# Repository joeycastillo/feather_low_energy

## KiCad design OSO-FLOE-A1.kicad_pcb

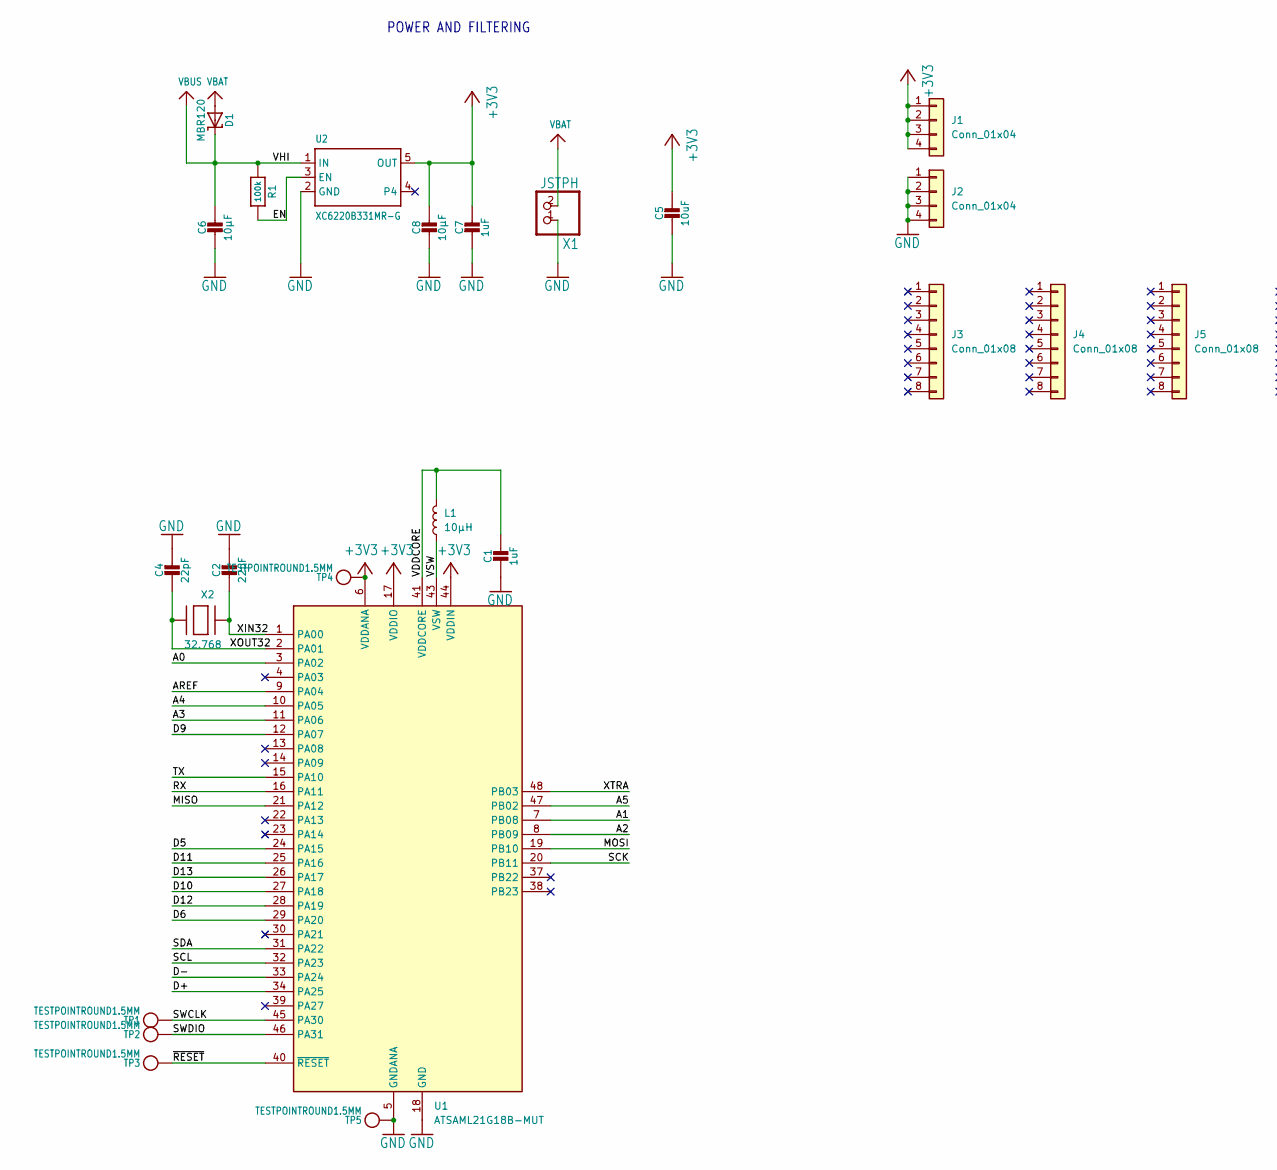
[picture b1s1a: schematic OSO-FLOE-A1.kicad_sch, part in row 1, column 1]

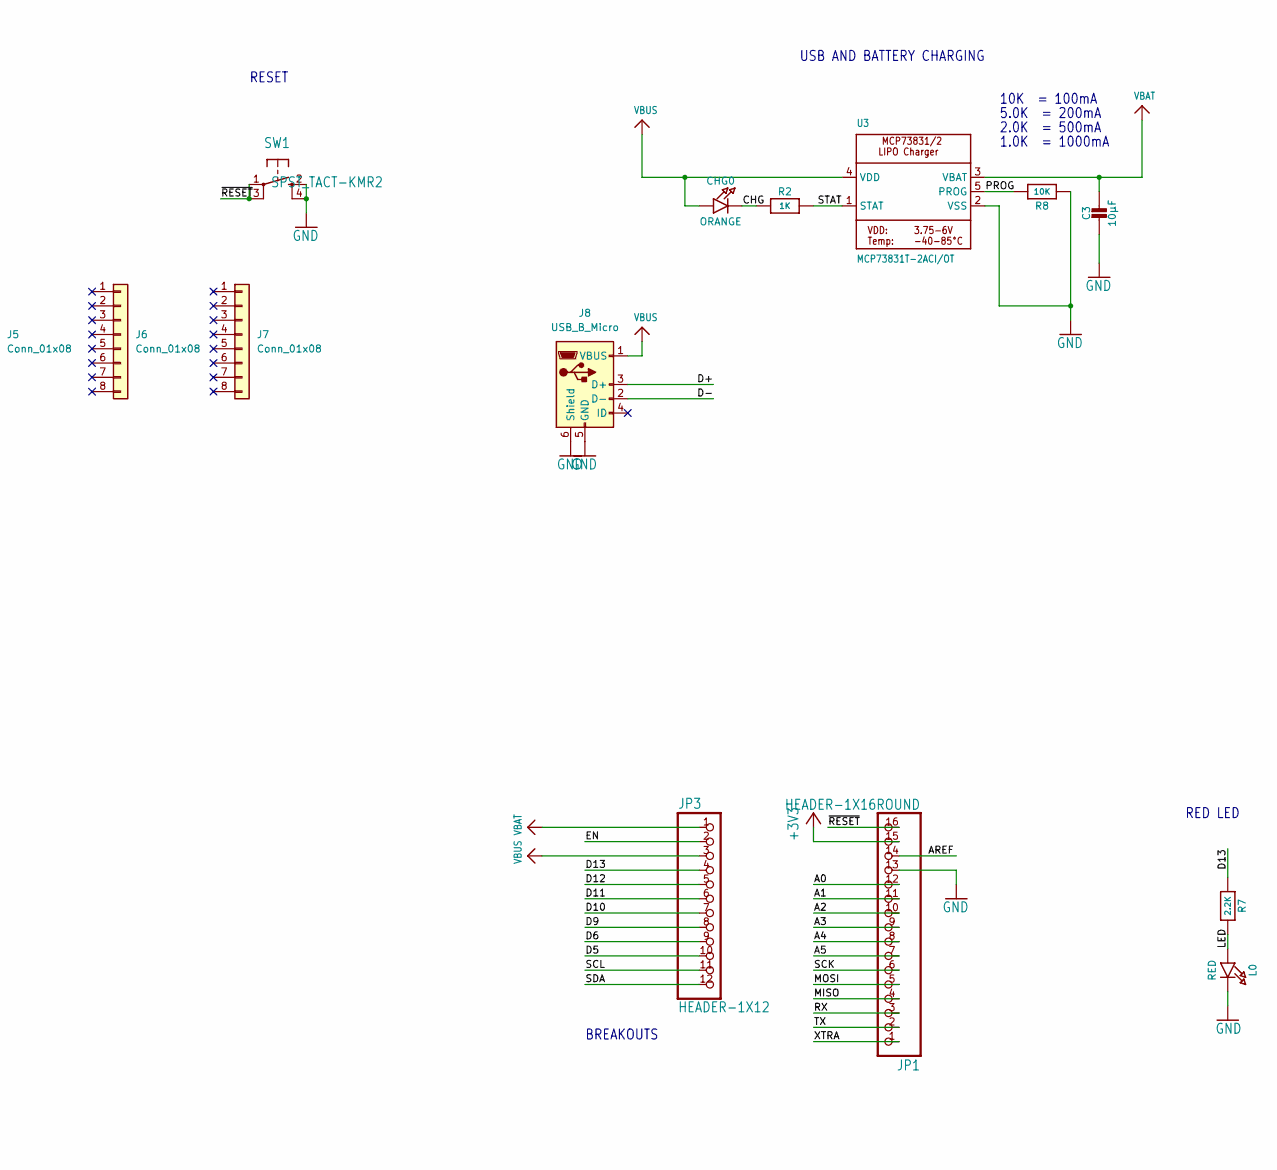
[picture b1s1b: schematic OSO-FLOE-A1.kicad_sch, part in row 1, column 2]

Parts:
C1, C7: 1uF; 0603-NO
C2, C4: 22pF; 0603-NO
C3, C6, C8: 10µF; 0805-NO
C5: 10uF; 0805-NO
CHG0: ORANGE; CHIPLED_0805_NOOUTLINE
D1: MBR120; SOD-123
J1, J2: Conn_01x04; PinHeader_1x04_P2.54mm_Vertical
J3, J4, J5, J6, J7: Conn_01x08; PinHeader_1x08_P2.54mm_Vertical
J8: USB_B_Micro; USB_Micro-B_Amphenol_10118194_Horizontal
JP1: HEADER-1X16ROUND; 1X16_ROUND
JP3: HEADER-1X12; 1X12_ROUND
L0: RED; CHIPLED_0805_NOOUTLINE
L1: 10µH; L_0805_2012Metric
R1: 100k; 0603-NO
R2: 1K; 0603-NO
R7: 2.2K; 0603-NO
R8: 10K; 0603-NO
SW1: SPST_TACT-KMR2; KMR2
TP1, TP2, TP3, TP4, TP5: TESTPOINTROUND1.5MM; TESTPOINT_ROUND_1.5MM
U1: ATSAML21G18B-MUT; QFN-48-1EP_7x7mm_P0.5mm_EP5.15x5.15mm
U2: XC6220B331MR-G; SOT23-5
U3: MCP73831T-2ACI/OT; SOT23-5
X1: JSTPH; JSTPH2
X2: 32.768; XTAL3215

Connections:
+3V3: C5.1, C7.1, C8.1, J1.1, J1.2, J1.3, J1.4, JP1.15, TP4.P$1, U1.6 (VDDANA), U1.17 (VDDIO), U1.36 (VDDIO), U1.44 (VDDIN), U2.5 (OUT)
/A0: JP1.12, U1.3 (PA02)
/A1: JP1.11, U1.7 (PB08)
/A2: JP1.10, U1.8 (PB09)
/A3: JP1.9, U1.11 (PA06)
/A4: JP1.8, U1.10 (PA05)
/A5: JP1.7, U1.47 (PB02)
/AREF: JP1.14, U1.9 (PA04)
/CHG: CHG0.C, R2.1
/D5: JP3.10, U1.24 (PA15)
/D6: JP3.9, U1.29 (PA20)
/D9: JP3.8, U1.12 (PA07)
/D10: JP3.7, U1.27 (PA18)
/D11: JP3.6, U1.25 (PA16)
/D12: JP3.5, U1.28 (PA19)
/D13: JP3.4, R7.1, U1.26 (PA17)
/D+: J8.3 (D+), U1.34 (PA25)
/D-: J8.2 (D-), U1.33 (PA24)
/EN: JP3.2, R1.2, U2.3 (EN)
/LED: L0.A, R7.2
/MISO: JP1.4, U1.21 (PA12)
/MOSI: JP1.5, U1.19 (PB10)
/PROG: R8.1, U3.5 (PROG)
/RX: JP1.3, U1.16 (PA11)
/SCK: JP1.6, U1.20 (PB11)
/SCL: JP3.11, U1.32 (PA23)
/SDA: JP3.12, U1.31 (PA22)
/STAT: R2.2, U3.1 (STAT)
/SWCLK: TP1.P$1, U1.45 (PA30)
/SWDIO: TP2.P$1, U1.46 (PA31)
/TX: JP1.2, U1.15 (PA10)
/VDDCORE: C1.1, L1.2, U1.41 (VDDCORE)
/VSW: L1.1, U1.43 (VSW)
/XIN32: C2.1, U1.1 (PA00), X2.P$1
/XOUT32: C4.1, U1.2 (PA01), X2.P$2
/XTRA: JP1.1, U1.48 (PB03)
/~RESET: JP1.16, SW1.1, SW1.3 (P1), TP3.P$1, U1.40 (~RESET)
GND: C1.2, C2.2, C3.2, C4.2, C5.2, C6.2, C7.2, C8.2, J2.1, J2.2, J2.3, J2.4, J8.5 (GND), J8.6 (Shield), JP1.13, L0.C, R8.2, SW1.2 (S), SW1.4 (S1), TP5.P$1, U1.5 (GNDANA), U1.18 (GND), U1.35 (GND), U1.42 (GND), U1.49, U2.2 (GND), U3.2 (VSS), X1.1
VBAT: C3.1, D1.A, JP3.1, U3.3 (VBAT), X1.2
VBUS: C6.1, CHG0.A, D1.C, J8.1 (VBUS), JP3.3, R1.1, U2.1 (IN), U3.4 (VDD)

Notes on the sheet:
RESET
2.0K = 500mA
10K = 100mA
5.0K = 200mA
POWER AND FILTERING
BREAKOUTS
1.0K = 1000mA
USB AND BATTERY CHARGING
RED LED

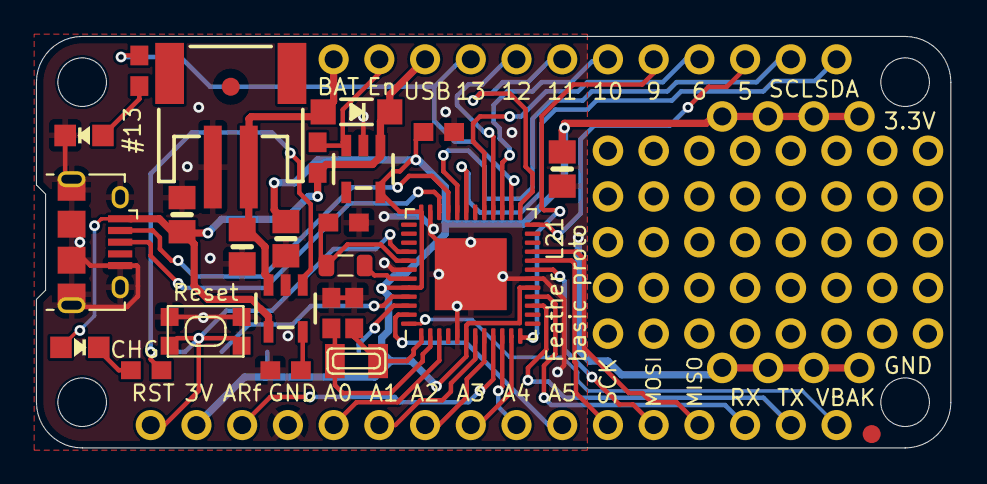
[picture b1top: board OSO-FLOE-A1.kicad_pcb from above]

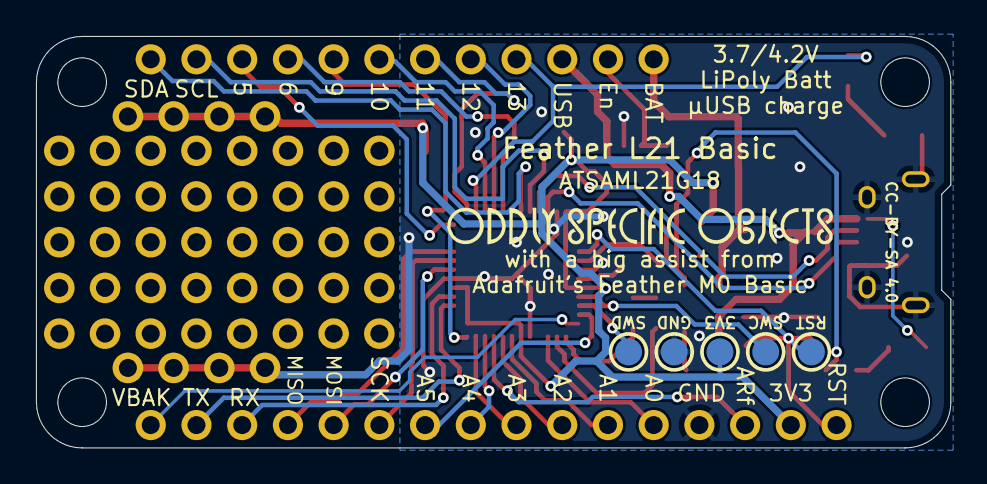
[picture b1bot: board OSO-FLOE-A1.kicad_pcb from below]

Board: 2 copper layers, 50.8 x 22.9 mm, 37 parts (5 on the bottom side), 40 nets.

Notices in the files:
OSO-FLOE-A1.kicad_pcb:
CC-BY-SA 4.0
